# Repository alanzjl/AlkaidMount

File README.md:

# Alkaid Mount - DIY Equatorial Mount with HarmonicDrive

Built by JZ.

For my build log, checkout [this page on my website](https://alanz.info/pages/alkaidmount.html).

The following YouTube video documents all the processes with no explaination:

The same video can also be found on [bilibili](https://www.bilibili.com/video/BV1SR4y1X7bt/?share_source=copy_web&vd_source=4d6f936f693563e28752aadac9dd326f).

- Note: do not directly use the dxf files under the Machine/ folder.
They are for reference only and they might contain duplicated parts, because I had to make several parts more than once due to some mistakes at the beginning.
I'd recommend looking at the solidworks files first and try to understand every part, then generate your own dxf.

## Introduction
AlkaidMount is a DIY aluminum HarmonicDrive German style equatorial mount with a ~25lbs unbalanced or >70lbs balanced load capacity, with a self weight of only ~16lbs.
Each axis consists of a 100:1 HarmonicDrive gearbox, followed by a 27:1 planetary gearbox, driven by a Nema17 stepper motor.

Weight capacity is calculated with gearbox load limits as well as rigid body simulation.
Note that I have not yet done any torture tests, so those numbers are all theoratical. 
I've only tested it on the two scopes I own - an unbalanced Williams Optics GT71 setup (~15lbs) and balanced a Meade LX200 8" SCT setup (~25lbs not including the counterweights).
Both setups worked beautifully.

This repo contains ALL the design files (CAD, manufacture drawings, PCB files, software) to make the AlkaidMount.
I made this repo public to inspire other ideas.
Due to the difficulty in sourcing the exact same model of the two HarmonicDrive's (unless you buy new:), replicating the exact same mount would be hard. 
However modifying this design to suite other HD models shouldn't be too hard.

## BOM - Hardware
-----------
| Name | Quantity | Drawings | Datasheet |
| -------- | -------- | -------- | -------- |
| Harmonic Drive CSF-17-100-2UH-LW | 2 | [Drawings](https://www.harmonicdrive.net/_hd/content/caddownloads/dxf/csf-2uh_gearheads/csf-17-xx-2uh.pdf) | [Datasheet](https://www.harmonicdrive.net/products/gear-units/gear-units/csf-2uh/csf-17-100-2uh) |
| Nema 17 with 27:1 Planetary Gearbox | 2 | [Drawings](https://www.omc-stepperonline.com/download/17HS19-1684S-PG27.pdf) | [Datasheet](https://www.omc-stepperonline.com/nema-17-stepper-motor-bipolar-l-48mm-w-gear-ratio-27-1-planetary-gearbox-17hs19-1684s-pg27) |
| 1/8" Aluminum plate | 12"x12" minimum | - | - |
| 1/4" Aluminum plate | - | - | - |
| M4x8 | many :) | - | - |
| M3x8 | not that many :] | - | - |
| M5x8 | a few :{ | - | - |

## BOM - Electronics
-----------
| Name | Quantity | Drawings | Datasheet |
| -------- | -------- | -------- | -------- |
| Teensy 4.0 | 1 | - | - |
| ESP-32 (for wifi control) | 1 | - | - |

For parts on the PCB, see [PCB/parts.txt](PCB/parts.txt).

## Manufacturing guide

Most parts were made with 2D waterjetting, with not too much post-processing (tab removal, tapping if needed).
Some parts have holes on the side, so some milling was involved.

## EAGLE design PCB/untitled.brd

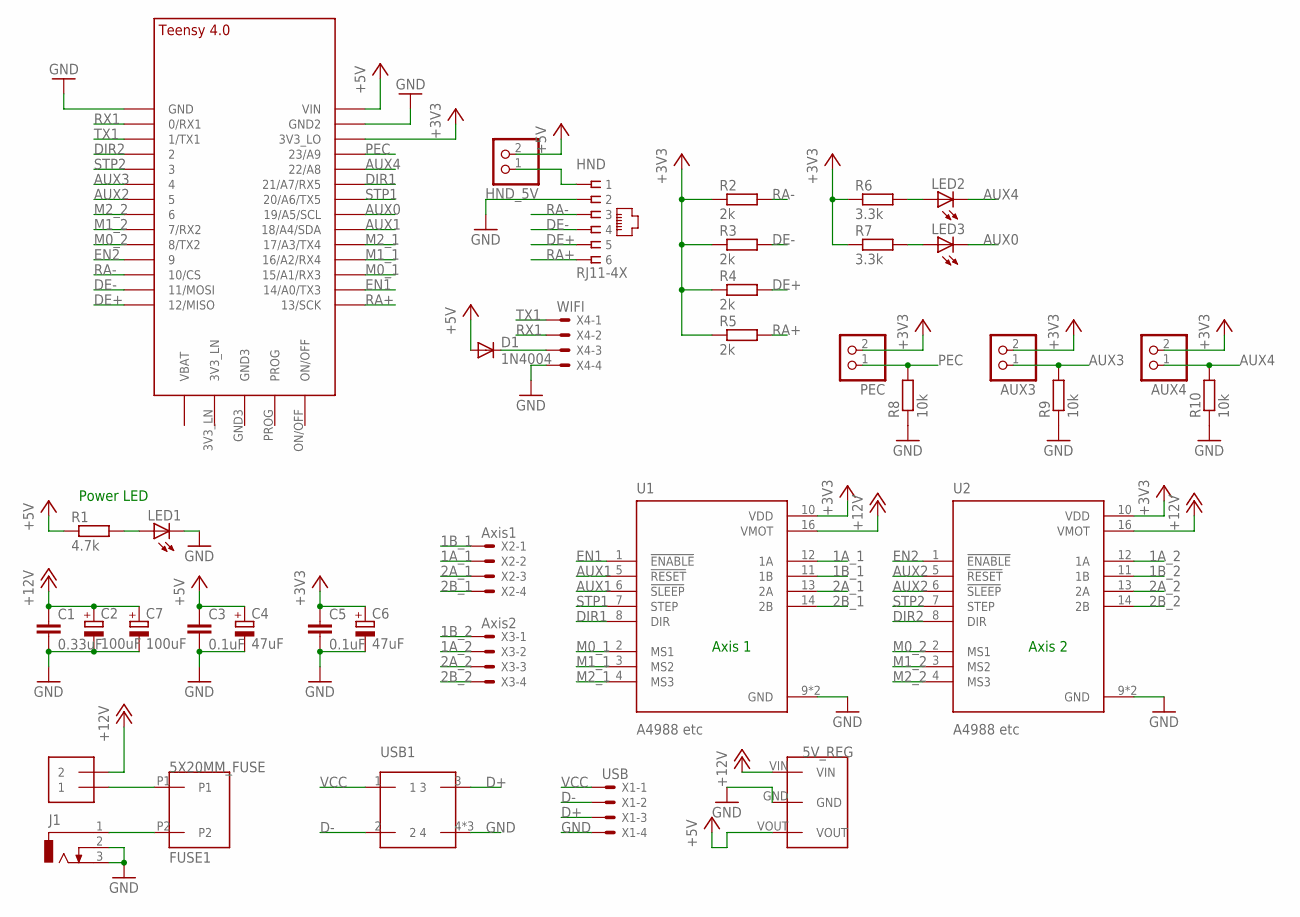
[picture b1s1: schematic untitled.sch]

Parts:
5V_REG: TSR_5V
AUX3, AUX4: PINHD-1X2; 1X02
C1: 0.33uF; C050-024X044
C2, C7: 100uF; E5-8,5
C3, C5: 0.1uF; C050-024X044
C4, C6: 47uF; E5-8,5
D1: 1N4004; DO41-10
FUSE1: 5X20MM_FUSE
HND: RJ11-4X; RJ11-NO_SHIELD
HND_5V: PINHD-1X2; 1X02
J1: DCJ0303
LED1, LED2, LED3: LED5MM
PEC: PINHD-1X2; 1X02
R1: 4.7k; 0207/7
R2, R3, R4, R5: 2k; 0207/7
R6, R7: 3.3k; 0207/7
R8, R9, R10: 10k; 0207/7
SWITCH: 1X2-3.5MM
U1, U2: A4988 etc; MODULE_A4988_STEPPER_MOTOR_DRIVER_CARRIER
U$1: TEENSY_4.0
USB1: USB-B_SOCKET
X1: USB; JST-XH-04-PACKAGE-ROUND-PAD
X2: Axis1; JST-XH-04-PACKAGE-LONG-PAD
X3: Axis2; JST-XH-04-PACKAGE-LONG-PAD
X4: WIFI; JST-XH-04-PACKAGE-LONG-PAD

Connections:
1A_1: U1.12 (1A), X2.2
1A_2: U2.12 (1A), X3.2
1B_1: U1.11 (1B), X2.1
1B_2: U2.11 (1B), X3.1
2A_1: U1.13 (2A), X2.3
2A_2: U2.13 (2A), X3.3
2B_1: U1.14 (2B), X2.4
2B_2: U2.14 (2B), X3.4
+3V3: AUX3.2, AUX4.2, C5.1, C6.+, PEC.2, R2.1, R3.1, R4.1, R5.1, R6.1, R7.1, U1.10 (VDD), U2.10 (VDD), U$1.3V3_LO
+5V: 5V_REG.VOUT, C3.1, C4.+, D1.A, HND_5V.2, R1.1, U$1.VIN
+12V: 5V_REG.VIN, C1.1, C2.+, C7.+, SWITCH.2, U1.16 (VMOT), U2.16 (VMOT)
AUX0: LED3.K (C), U$1.19/A5/SCL
AUX1: U1.5 (!RESET), U1.6 (!SLEEP), U$1.18/A4/SDA
AUX2: U2.5 (!RESET), U2.6 (!SLEEP), U$1.5
AUX3: AUX3.1, R9.2, U$1.4/CANRX (4)
AUX4: AUX4.1, LED2.K (C), R10.2, U$1.22/A8
D+: USB1.3, X1.3
D-: USB1.2, X1.2
DE+: HND.5, R4.2, U$1.12/MISO
DE-: HND.4, R3.2, U$1.11/MOSI
DIR1: U1.8 (DIR), U$1.21/A7 (21/A7/RX5)
DIR2: U2.8 (DIR), U$1.2
EN1: U1.1 (!ENABLE), U$1.14/A0 (14/A0/TX3)
EN2: U2.1 (!ENABLE), U$1.9/CS (9)
GND: 5V_REG.GND, C1.2, C2.-, C3.2, C4.-, C5.2, C6.-, C7.-, HND.2, J1.2, J1.3, LED1.K (C), R8.1, R9.1, R10.1, U1.9 (GND), U1.15 (GND), U2.9 (GND), U2.15 (GND), U$1.GND, U$1.GND2, USB1.4, USB1.P$1 (4), USB1.P$2 (4), X1.4, X4.4
M0_1: U1.2 (MS1), U$1.15/A1 (15/A1/RX3)
M0_2: U2.2 (MS1), U$1.8 (8/TX2)
M1_1: U1.3 (MS2), U$1.16/A2 (16/A2/RX4)
M1_2: U2.3 (MS2), U$1.7 (7/RX2)
M2_1: U1.4 (MS3), U$1.17/A3 (17/A3/TX4)
M2_2: U2.4 (MS3), U$1.6
unnamed: FUSE1.P2, J1.1
unnamed: FUSE1.P1, SWITCH.1
unnamed: LED1.A, R1.2
unnamed: D1.C, X4.3
unnamed: HND.1, HND_5V.1
unnamed: LED2.A, R6.2
unnamed: LED3.A, R7.2
PEC: PEC.1, R8.2, U$1.23/A9
RA+: HND.6, R5.2, U$1.13/SCK
RA-: HND.3, R2.2, U$1.10/CS
RX1: U$1.0/RX (0/RX1), X4.2
STP1: U1.7 (STEP), U$1.20/A6 (20/A6/TX5)
STP2: U2.7 (STEP), U$1.3/CANTX (3)
TX1: U$1.1/TX (1/TX1), X4.1
VCC: USB1.1, X1.1

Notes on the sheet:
Power LED
Axis 1
Axis 2

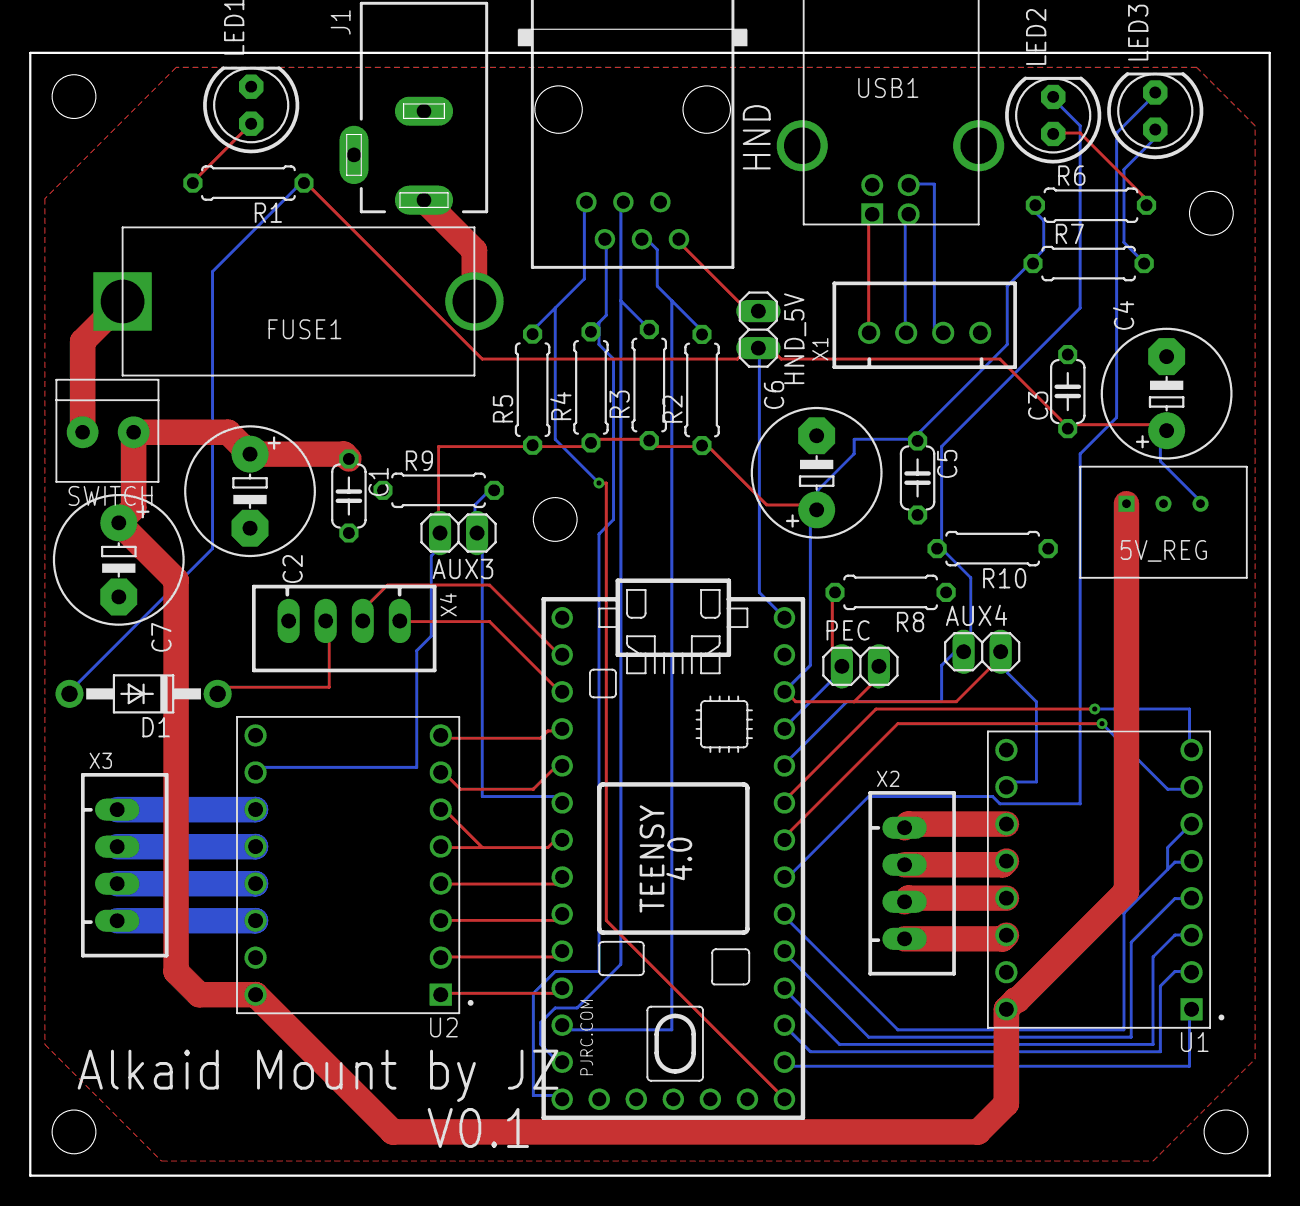
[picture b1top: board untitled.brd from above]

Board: 2 copper layers, 85.0 x 78.5 mm, 38 parts (0 on the bottom side), 46 nets.

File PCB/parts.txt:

Partlist

Exported from untitled.sch at 10/31/2022 12:25 AM

EAGLE Version 9.6.2 Copyright (c) 1988-2020 Autodesk, Inc.

Assembly variant: 

Part     Value          Device                             Package                                   Library                            Sheet

5V_REG   TSR_5V         TSR_5V                             TSR_5V                                    alans_lbr                          1
AUX3                    PINHD-1X2                          1X02                                      pinhead                            1
AUX4                    PINHD-1X2                          1X02                                      pinhead                            1
C1       0.33uF         C-EU050-024X044                    C050-024X044                              rcl                                1
C2       100uF          CPOL-EUE5-8.5                      E5-8,5                                    rcl                                1
C3       0.1uF          C-EU050-024X044                    C050-024X044                              rcl                                1
C4       47uF           CPOL-EUE5-8.5                      E5-8,5                                    rcl                                1
C5       0.1uF          C-EU050-024X044                    C050-024X044                              rcl                                1
C6       47uF           CPOL-EUE5-8.5                      E5-8,5                                    rcl                                1
C7       100uF          CPOL-EUE5-8.5                      E5-8,5                                    rcl                                1
D1       1N4004         1N4004                             DO41-10                                   adafruit                           1
FUSE1    5X20MM_FUSE    5X20MM_FUSE                        5X20MM_FUSE                               alans_lbr                          1
HND      RJ11-4X        RJ11-4X                            RJ11-NO_SHIELD                            con-tycoelectronics                1
HND_5V                  PINHD-1X2                          1X02                                      pinhead                            1
J1                      DCJ0303                            DCJ0303                                   con-jack                           1
LED1                    LED5MM                             LED5MM                                    adafruit                           1
LED2                    LED5MM                             LED5MM                                    adafruit                           1
LED3                    LED5MM                             LED5MM                                    adafruit                           1
PEC                     PINHD-1X2                          1X02                                      pinhead                            1
R1       4.7k           R-EU_0207/7                        0207/7                                    rcl                                1
R2       2k             R-EU_0207/7                        0207/7                                    rcl                                1
R3       2k             R-EU_0207/7                        0207/7                                    rcl                                1
R4       2k             R-EU_0207/7                        0207/7                                    rcl                                1
R5       2k             R-EU_0207/7                        0207/7                                    rcl                                1
R6       3.3k           R-EU_0207/7                        0207/7                                    rcl                                1
R7       3.3k           R-EU_0207/7                        0207/7                                    rcl                                1
R8       10k            R-EU_0207/7                        0207/7                                    rcl                                1
R9       10k            R-EU_0207/7                        0207/7                                    rcl                                1
R10      10k            R-EU_0207/7                        0207/7                                    rcl                                1
SWITCH   1X2-3.5MM      1X2-3.5MM                          1X2-3.5MM                                 adafruit                           1
U$1      TEENSY_4.0     TEENSY_4.0                         TEENSY_4.0                                TEENSY 4.0                         1
U1       A4988 etc      A4988_STEPPER_MOTOR_DRIVER_CARRIER MODULE_A4988_STEPPER_MOTOR_DRIVER_CARRIER A4988_STEPPER_MOTOR_DRIVER_CARRIER 1
U2       A4988 etc      A4988_STEPPER_MOTOR_DRIVER_CARRIER MODULE_A4988_STEPPER_MOTOR_DRIVER_CARRIER A4988_STEPPER_MOTOR_DRIVER_CARRIER 1
USB1     USB-B_SOCKET   USB-B_SOCKET                       USB-B_SOCKET                              alans_lbr                          1
X1       USB            JST-XH-04-PIN-ROUND-PAD            JST-XH-04-PACKAGE-ROUND-PAD               JST_XH_Connectors                  1
X2       Axis1          JST-XH-04-PIN-LONG-PAD             JST-XH-04-PACKAGE-LONG-PAD                JST_XH_Connectors                  1
X3       Axis2          JST-XH-04-PIN-LONG-PAD             JST-XH-04-PACKAGE-LONG-PAD                JST_XH_Connectors                  1
X4       WIFI           JST-XH-04-PIN-LONG-PAD             JST-XH-04-PACKAGE-LONG-PAD                JST_XH_Connectors                  1

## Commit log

2022-07-05 finish pcb design
2022-07-06 fix hole size WIP, add some drawings
2022-07-12 update dimension for plate thickness
2022-07-13 add drawings
2022-07-30 add final cad
2022-10-31 add readme and other stuff
2022-10-31 fix youtube link
2023-12-11 update link
